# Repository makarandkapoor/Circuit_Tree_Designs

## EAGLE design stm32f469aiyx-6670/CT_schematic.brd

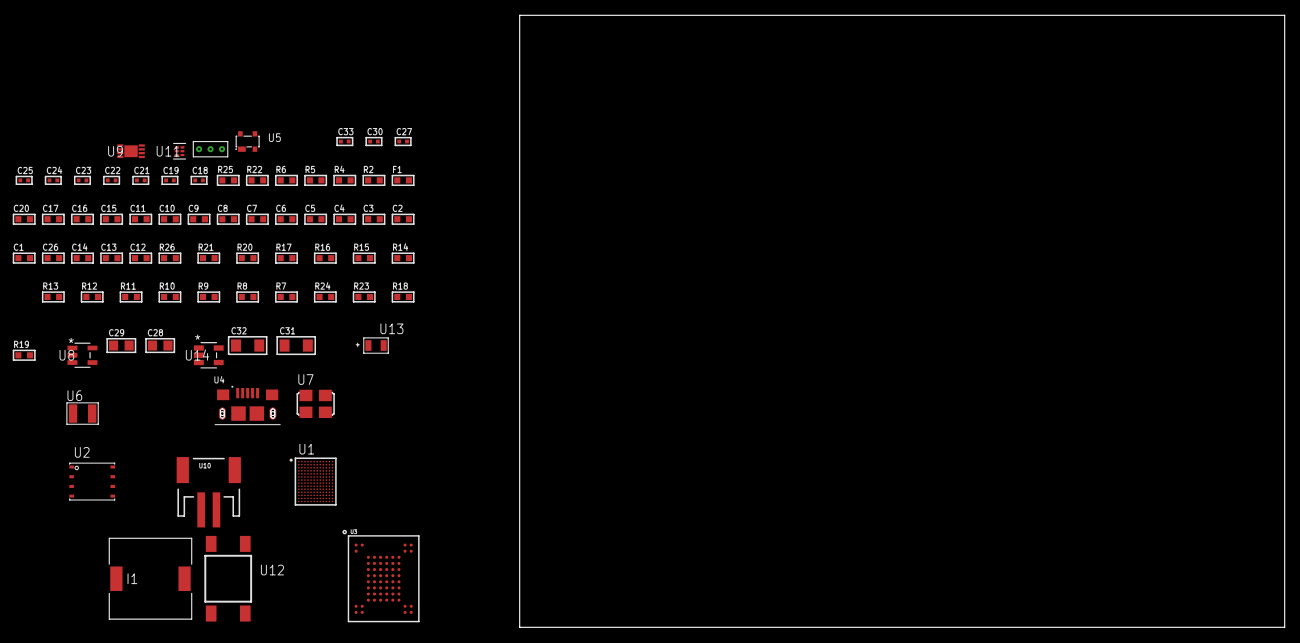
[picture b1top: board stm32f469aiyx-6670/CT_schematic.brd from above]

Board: 2 copper layers, 74 parts (0 on the bottom side), 48 nets, no tracks yet.

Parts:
C1, C16, C20: 1e-06; C0603
C2, C3, C4, C5, C6, C7, C8, C9, C10, C11, C17: 1e-07; C0603
C12: 4.7e-06; C0603
C13, C14, C26: 2.2e-06; C0603
C15: 1e-08; C0603
C18, C19: 1e-11; C0402
C21, C27, C33: 1e-08; C0402
C22, C23, C24, C25, C30: 1e-07; C0402
C28, C29: 1e-05; C0805
C31, C32: 1e-05; C1206
F1: 240.0; L0603
I1: 2.5e-06; DR1040
R2: 1000.0; R0603
R4: 4700.0; R0603
R5, R6: 2200.0; R0603
R7, R8, R9, R10, R11, R12, R13, R14, R15, R16, R17, R20, R21, R26: 10000.0; R0603
R18: 220000.0; R0603
R19: 1000000.0; R0603
R22: 9100.0; R0603
R23: 680000.0; R0603
R24: 120000.0; R0603
R25: 2000.0; R0603
U1: STM32F469AIY6TR; WLCSP168
U2: 24AA512-I/MF; DFN8-S
U3: mt29f4g08abadah4; VFBGA-63
U4: 10118193-0001LF; FCI_10118193-0001LF
U5: prtr5v0u2ax; SOT143B
U6: ABS07-32.768KHZ-7-T
U7: ASFL1-25MHZ-NCS; ASFL1
U8: ltc3406es5; TSOT-23-5
U9: MCP73831T-2ACI/MC; DFN8_2X3MC
U10: S2B-PH-SM4-TB(LF)(SN); JST-2-SMD
U11: TPS3895ADRYR; SON-6
U12: 4-1437565-2; SW_4-1437565-2
U13: Q65110A2395; LGM67K-G1J2-24-Z
U14: nc7sz125m5x; NC7SZ125M5X
U15: Dummy; DUMMY_PACKAGE_165

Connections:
CLK_CRYSTAL_U1_E11: C18.1, U1.E11, U6.1
CLK_CRYSTAL_U1_E12: C19.1, U1.E12, U6.2
CLK_U1_K11: U1.K11, U7.3
GND: C1.2, C2.2, C3.2, C4.2, C5.2, C6.2, C7.2, C8.2, C9.2, C10.2, C11.2, C12.2, C13.2, C14.2, C15.2, C16.2, C17.2, C18.2, C19.2, C20.2, C21.2, C22.2, C23.2, C24.2, C25.2, C26.2, C27.2, C28.2, C29.1, C29.2, C30.2, C31.2, C32.2, C33.2, R2.2, R9.2, R10.2, R11.2, R18.2, R22.2, R24.2, R25.2, U1.A4, U1.B7, U1.B10, U1.C1, U1.F2, U1.F7, U1.F12, U1.H1, U1.H7, U1.J11, U1.L11, U1.M1, U1.N8, U1.N11, U1.P4, U2.4, U3.C5, U3.F7, U3.K3, U3.K8, U4.5, U4.6, U4.7, U4.8, U4.9, U5.1, U7.2, U8.2, U9.6, U9.9, U10.2, U11.2, U13.C, U14.1, U14.3, U15.1
INPUT_USBPOWER_5V: C20.1, C31.1, R26.2, U1.E2, U4.1, U5.4, U9.1, U9.2
NET_U1_A9: R6.1, U1.A9, U2.5
NET_U1_B9: R5.1, U1.B9, U2.6
NET_U1_D2: C14.1, U1.D2
NET_U1_D9: R7.1, U1.D9
NET_U1_F8: R8.1, U1.F8
NET_U1_H9: R4.1, U1.H9, U14.4
NET_U1_M12: C15.1, C16.1, F1.1, U1.M12
NET_U1_N4: C13.1, U1.N4
NET_U1_P9: R9.1, U1.P9
NET_U1_P11: U12.3, U12.4
NET_U2_1: R10.1, U2.1
NET_U2_2: R11.1, U2.2
NET_U2_3: R12.1, U2.3
NET_U3_C3: R17.1, U3.C3
NET_U8_3: I1.1, U8.3
NET_U8_5: R18.1, R19.1, U8.5
NET_U8_ATNET_3: I1.2, R19.2
NET_U9_5: R26.1, U9.5
NET_U9_8: R25.1, U9.8
NET_U11_1: R21.1, R22.1, U11.1
NET_U11_3: R23.2, R24.1, U11.3
NET_U11_4: R20.1, U11.4, U14.2
NET_U12_1: R2.1, U12.1, U12.2
PROC_ADC1_IN3: U1.N10, U15.2
PROC_ADC1_IN4: U1.M9, U15.3
PROC_FMC_A16: U1.J4, U3.D5
PROC_FMC_A17: U1.M2, U3.C4
PROC_FMC_D0: U1.L3, U3.H4
PROC_FMC_D1: U1.L2, U3.J4
PROC_FMC_D2: U1.E6, U3.K4
PROC_FMC_D3: U1.A3, U3.K5
PROC_FMC_D4: U1.N7, U3.K6
PROC_FMC_D5: U1.M7, U3.J7
PROC_FMC_D6: U1.K6, U3.K7
PROC_FMC_D7: U1.P6, U3.J8
PROC_FMC_INT: R13.1, U1.H6, U3.C8
PROC_FMC_NCE: R14.1, U1.D7, U3.C6
PROC_FMC_NOE: R16.1, U1.B4, U3.D4
PROC_FMC_NWE: R15.1, U1.C6, U3.C7
PROC_USB_OTG_FS_DM: U1.F7, U4.2, U5.3
PROC_USB_OTG_FS_DP: U1.F6, U4.3, U5.2
VCC_S1_3V7: C28.1, C32.1, U8.4, U9.3, U9.4, U10.1
VCC_TIER1_3V3: C1.1, C2.1, C3.1, C4.1, C5.1, C6.1, C7.1, C8.1, C9.1, C10.1, C11.1, C12.1, C17.1, C21.1, C22.1, C23.1, C24.1, C25.1, C26.1, C27.1, C29.2, C30.1, C33.1, F1.2, I1.2, R4.2, R5.2, R6.2, R7.2, R8.2, R12.2, R13.2, R14.2, R15.2, R16.2, R17.2, R19.2, R20.2, R21.2, R23.1, U1.A7, U1.A11, U1.B5, U1.C2, U1.C12, U1.F1, U1.G11, U1.J12, U1.L1, U1.P3, U1.P8, U1.P12, U2.7, U2.8, U3.D3, U3.G4, U3.H8, U3.J6, U7.4, U11.6, U14.5

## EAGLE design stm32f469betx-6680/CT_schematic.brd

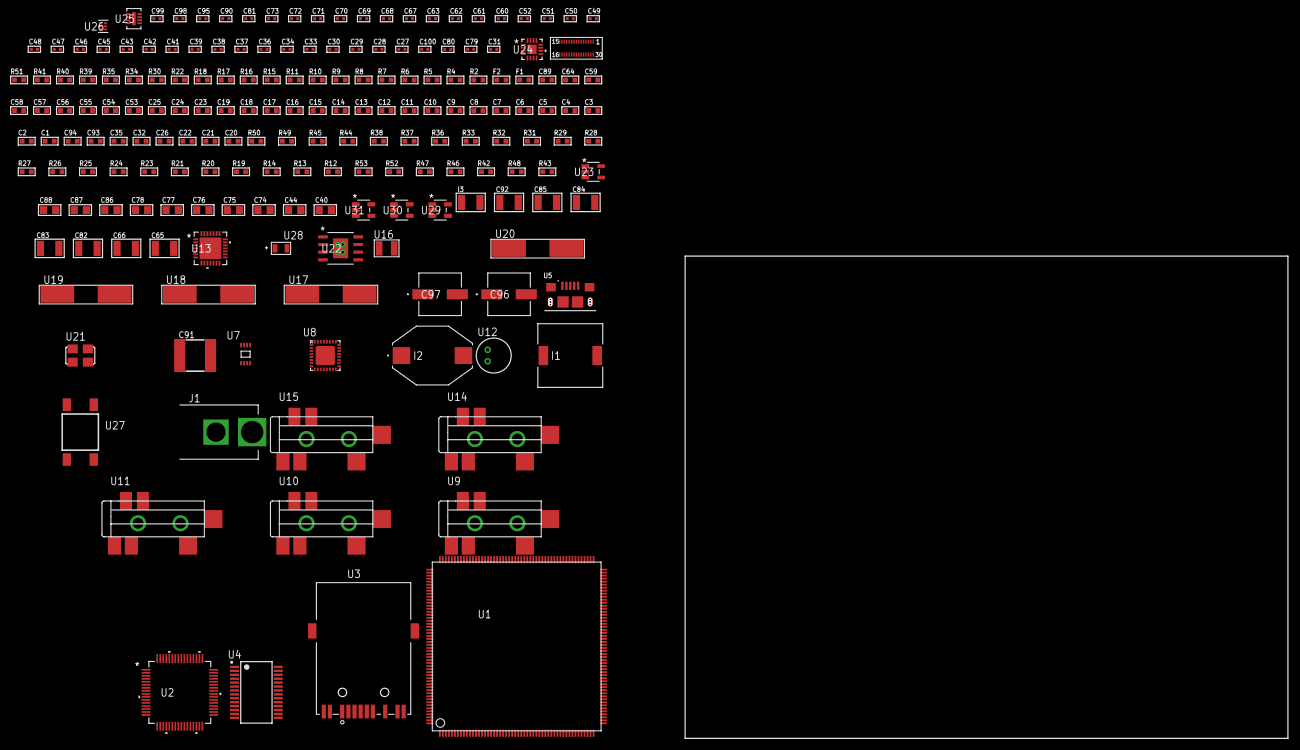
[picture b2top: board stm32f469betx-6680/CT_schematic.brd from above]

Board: 2 copper layers, 122.6 x 80.0 mm, 188 parts (0 on the bottom side), 129 nets, no tracks yet.

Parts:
C1, C24, C53, C54, C55, C56, C57, C58, C59, C64, C89: 1e-06; C0603
C2, C3, C4, C5, C6, C7, C8, C9, C10, C11, C12, C13, C14, C15, C16, C17, C18, C19, C25: 1e-07; C0603
C20: 4.7e-06; C0603
C21, C22, C26, C32, C35, C93: 2.2e-06; C0603
C23: 1e-08; C0603
C27, C28, C29, C30: 1e-11; C0402
C31: 1.8e-08; C0402
C33, C36, C38, C39, C41, C42, C43, C45, C46, C47, C48, C49, C50, C51, C60, C61, C62, C63, C69, C70, C71, C72, C73, C90, C95: 1e-07; C0402
C34, C37, C52, C81, C98, C99, C100: 1e-08; C0402
C40, C74, C75, C76, C77, C78, C86, C87, C88: 1e-05; C0805
C44: 4.7e-06; C0805
C65, C66: 2.2e-05; C1210
C67, C68: 1e-09; C0402
C79, C80: 2.2e-11; C0402
C82, C83, C84, C85, C92: 1e-05; C1210
C91: 6.8e-05; 2220
C94: 2.2e-07; C0603
C96, C97: 0.0001; EXV-9H
F1: 240.0; L0603
F2: 510.0; L0603
I1: 7e-06; DR1040
I2: 1.5e-06; IND_PM3316
I3: 1e-05; L1210
J1: PJ-037B; PJ-037B_PACKAGE
R2: 1000.0; R0603
R4, R5, R6, R30: 4700.0; R0603
R7, R8, R9, R10, R11, R41: 2200.0; R0603
R12, R13, R14, R19, R20, R21, R23, R24, R25, R26, R27, R28, R29, R31, R32, R33, R49, R50: 10000.0; R0603
R15, R16: 0.1; R0603
R17, R18: 200.0; R0603
R22, R34, R35: 1270.0; R0603
R36, R37, R38: 47000.0; R0603
R39: 680.0; R0603
R40: 910.0; R0603
R42: 270000.0; R0603
R43: 1000000.0; R0603
R44: 20000.0; R0603
R45: 91000.0; R0603
R46: 300000.0; R0603
R47: 100000.0; R0603
R48: 1600000.0; R0603
R51: 9100.0; R0603
R52: 680000.0; R0603
R53: 120000.0; R0603
U1: STM32F469BET6; LQFP208
U2: BCM5221KPT; TQFP64_10X10MC
U3: 7498011122R
U4: FT232RL-REEL; SSOP-28
U5: 10118193-0001LF; FCI_10118193-0001LF
U6: LH430WV2-SD01
U7: 24AA04-I/MC; TDFN-8/6MM
U8: SGTL5000XNAA3; QFN-32
U9, U10, U11, U14, U15: SJ-43515TS-SMT-TR
U12: WM-64PCT; WM-64PC
U13: WM8731CLSEFL; QFN-28
U16: ABS07-32.768KHZ-7-T
U17, U18: ABLS-25.000MHZ-B2F-T
U19: ABLS-12.000MHZ-B4-T
U20: ABLS-12.288MHZ-B4-T
U21: ASFL-24.57MHZ-NCS; ASFL1
U22: MIC5234YME; SOIC-8_EP
U23: ltc3406es5; TSOT-23-5
U24: LTC3601EUD#PBF; QFN-16_EP
U25: LT3494AEDDB#TRMPBF; DFN-8_DDB
U26: TPS3895ADRYR; SON-6
U27: 4-1437565-2; SW_4-1437565-2
U28: Q65110A2395; LGM67K-G1J2-24-Z
U29, U30, U31: nc7sz125m5x; NC7SZ125M5X

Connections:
CLK_CRYSTAL_U1_9: C27.1, U1.9, U16.1
CLK_CRYSTAL_U1_10: C28.1, U1.10, U16.2
CLK_CRYSTAL_U1_32: C29.1, U1.32, U17.1
CLK_CRYSTAL_U1_33: C30.1, U1.33, U17.2
CLK_CRYSTAL_U2_5: U2.5, U18.2
CLK_CRYSTAL_U2_6: U2.6, U18.1
CLK_CRYSTAL_U4_27: U4.27, U19.1
CLK_CRYSTAL_U4_28: U4.28, U19.2
CLK_CRYSTAL_U13_1: C79.1, U13.1, U20.1
CLK_CRYSTAL_U13_2: C80.1, U13.2, U20.2
CLK_U8_21: U8.21, U21.3
GND: C1.2, C2.2, C3.2, C4.2, C5.2, C6.2, C7.2, C8.2, C9.2, C10.2, C11.2, C12.2, C13.2, C14.2, C15.2, C16.2, C17.2, C18.2, C19.2, C20.2, C21.2, C22.2, C23.2, C24.2, C25.2, C26.2, C27.2, C28.2, C29.2, C30.2, C31.2, C32.2, C33.2, C34.2, C35.2, C36.2, C37.2, C38.2, C39.2, C40.2, C41.2, C42.2, C43.2, C44.2, C45.2, C46.2, C47.2, C48.2, C49.2, C50.2, C51.2, C52.2, C60.2, C61.2, C62.2, C63.2, C64.2, C68.2, C69.2, C70.2, C71.2, C72.2, C73.2, C74.2, C75.2, C76.2, C77.2, C78.2, C79.2, C80.2, C81.2, C82.2, C83.2, C84.2, C85.2, C86.2, C87.1, C87.2, C88.2, C89.2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
NET_U1_34: R6.1, U1.34, U31.4
NET_U1_36: R9.1, U1.36, U2.42
NET_U1_42: C23.1, C24.1, F1.1, U1.41, U1.42
NET_U1_45: R10.1, U1.45, U2.41
NET_U1_63: R14.1, U1.63
NET_U1_92: C21.1, U1.92
NET_U1_125: C26.1, U1.119, U1.125
NET_U1_148: C22.1, U1.148
NET_U1_195: R7.1, U1.195, U7.6
NET_U1_196: R8.1, U1.196, U7.5
NET_U1_197: R13.1, U1.197
NET_U1_203: R12.1, U1.203
NET_U1_208: U27.3, U27.4
NET_U2_2: C35.1, C36.1, C37.1, U2.2, U2.55
NET_U2_9: R5.1, U2.9, U30.4
NET_U2_10: R23.1, U2.10
NET_U2_11: R24.1, U2.11
NET_U2_12: R25.1, U2.12
NET_U2_13: R26.1, U2.13
NET_U2_14: R27.1, U2.14
NET_U2_16: R21.1, U2.16
NET_U2_18: R29.1, U2.18
NET_U2_23: R22.1, U2.23
NET_U2_27: C32.1, C33.1, C34.1, U2.22, U2.27, U2.28
NET_U2_37: R28.1, U2.37
NET_U2_38: R19.1, U2.38
NET_U2_39: R20.1, U2.39
NET_U3_1: U2.31, U3.1
NET_U3_2: F2.2, U3.2
NET_U3_3: U2.30, U3.3
NET_U3_4: U2.26, U3.4
NET_U3_5: C31.1, F2.1, U3.2, U3.5
NET_U3_6: U2.25, U3.6
NET_U3_8: R16.1, U3.8
NET_U3_9: R17.1, U3.9
NET_U3_11: R18.1, U3.11
NET_U3_12: R17.2, U3.12
NET_U3_13: R15.1, U3.13, U3.14
NET_U4_14: R31.1, U4.14
NET_U4_17: C45.1, U4.17
NET_U4_19: R32.1, U4.19
NET_U5_1: R30.1, U5.1
NET_U5_2: U4.16, U5.2
NET_U5_3: U4.15, U5.3
NET_U6_4: R4.1, U6.4, U29.4
NET_U6_20: R33.1, U6.20
NET_U8_10: C63.1, U8.10
NET_U8_29: R34.1, U8.29
NET_U8_31: R35.1, U8.31
NET_U9_1: U8.4, U9.1
NET_U9_2: U8.2, U9.2
NET_U9_5: U8.6, U9.5
NET_U10_2: C54.1, U10.2
NET_U10_5: C53.1, U10.5
NET_U11_2: C56.1, C57.1, U11.2
NET_U11_5: C55.1, U11.5
NET_U11_13: C56.2, C57.2
NET_U12_1: C58.1, C59.1, C64.1, U8.16, U12.1
NET_U12_15: C58.2, C59.2
NET_U13_20: C73.1, C78.1, U13.20
NET_U14_2: C66.1, R37.1, U14.2
NET_U14_5: C65.1, R36.1, U14.5
NET_U15_5: C67.1, C68.1, R38.1, R39.1, U15.5
NET_U22_4: R40.2, R41.1, U22.4
NET_U23_3: I1.1, U23.3
NET_U23_5: R42.1, R43.1, U23.5
NET_U23_ATNET_3: I1.2, R43.2
NET_U24_3: C90.2, I2.1, U24.3, U24.4
NET_U24_6: C90.1, U24.6
NET_U24_7: C89.1, U24.7, U24.12
NET_U24_10: R46.1, U24.10
NET_U24_11: R44.1, R45.1, U24.11
NET_U24_ATNET_3: I2.2, R45.2
NET_U25_1: I3.1, U25.1
NET_U25_5: R47.1, U25.5
NET_U25_6: R48.1, U25.6
NET_U25_8: C94.1, U25.8
NET_U26_1: R50.1, R51.1, U26.1
NET_U26_3: R52.2, R53.1, U26.3
NET_U26_4: R49.1, U26.4, U29.2, U30.2, U31.2
NET_U27_1: R2.1, U27.1, U27.2
PROC_DSIHOST_CKN: U1.124, U6.13
PROC_DSIHOST_CKP: U1.123, U6.14
PROC_DSIHOST_D0N: U1.121, U6.7
PROC_DSIHOST_D0P: U1.120, U6.8
PROC_DSIHOST_D1N: U1.127, U6.10
PROC_DSIHOST_D1P: U1.126, U6.11
PROC_ETH_COL: U1.47, U2.61
PROC_ETH_CRS: U1.43, U2.62
PROC_ETH_RXD0: U1.57, U2.48
PROC_ETH_RXD1: U1.58, U2.47
PROC_ETH_RXD2: U1.61, U2.44
PROC_ETH_RXD3: U1.62, U2.43
PROC_ETH_RX_CLK: U1.44, U2.50
PROC_ETH_RX_DV: U1.56, U2.49
PROC_ETH_RX_ER: U1.12, U2.51
PROC_ETH_TXD0: U1.104, U2.57
PROC_ETH_TXD1: U1.105, U2.58
PROC_ETH_TXD2: U1.37, U2.59
PROC_ETH_TXD3: U1.1, U2.60
PROC_ETH_TX_CLK: U1.38, U2.53
PROC_ETH_TX_EN: U1.91, U2.56
PROC_I2S2_CK: U1.90, U8.24
PROC_I2S2_EXT_SD: U1.106, U8.25
PROC_I2S2_SD: U1.107, U8.26
PROC_I2S2_WS: U1.154, U8.23
PROC_I2S3_CK: U1.192, U13.7
PROC_I2S3_EXT_SD: U1.193, U13.10
PROC_I2S3_SD: U1.163, U13.8
PROC_I2S3_WS: U1.53, U13.9, U13.11
PROC_UART4_RX: U1.162, U4.1
PROC_UART4_TX: U1.161, U4.5
VCC_S1_4V6: C82.1, C83.1, C86.1, C88.1, C92.1, C96.1, C97.1, I3.2, J1.1, R47.2, U22.5, U22.8, U23.4, U24.15, U24.16, U25.3, U25.4
VCC_TIER1_1V5: C60.1, C84.1, C85.1, R40.1, U6.29, U8.30, U22.1
VCC_TIER1_2V8: C49.1, C50.1, C51.1, C87.2, I1.2, R43.2, U6.16, U6.21, U6.22, U6.23
VCC_TIER1_3V3: C1.1, C2.1, C3.1, C4.1, C5.1, C6.1, C7.1, C8.1, C9.1, C10.1, C11.1, C12.1, C13.1, C14.1, C15.1, C16.1, C17.1, C18.1, C19.1, C20.1, C25.1, C38.1, C39.1, C40.1, C41.1, C42.1, C43.1, C44.1, C46.1, C47.1, C52.1, C61.1, C62.1, C69.1, C70.1, C71.1, C72.1, C74.1, C75.1, C76.1, C77.1, C81.1, C91.2, C95.1, C98.1, C99.1, C100.1, F1.2, I2.2, R4.2, R5.2, R6.2, R7.2, R8.2, R9.2, R10.2, R11.2, R12.2, R13.2, R20.2, R24.2, R29.2, R31.2, R34.2, R45.2, R49.2, R50.2, R52.1, U1.6, U1.15, U1.26, U1.39, U1.52, U1.59, U1.73, U1.83, U1.94, U1.103, U1.115, U1.118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
VCC_TIER1_12V0: C48.1, C93.1, R48.2, U6.30, U25.7

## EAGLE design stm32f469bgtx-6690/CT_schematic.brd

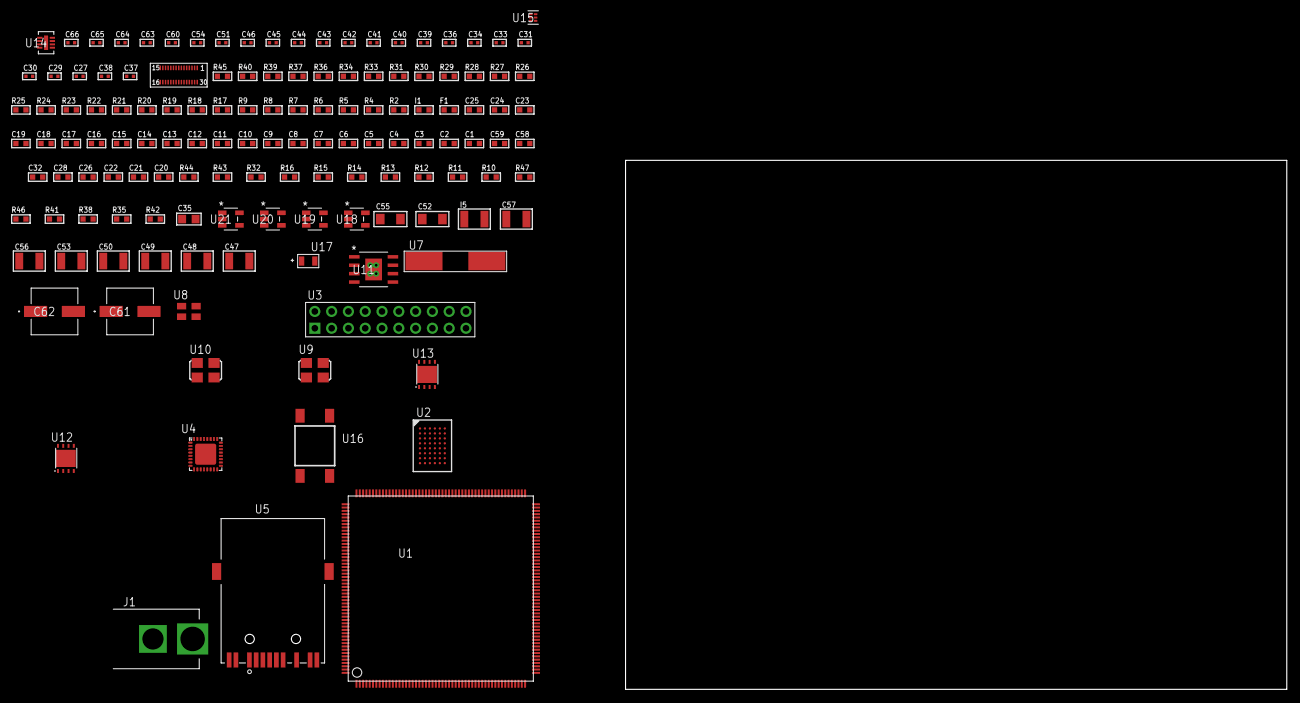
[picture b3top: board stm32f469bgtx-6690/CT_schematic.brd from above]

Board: 2 copper layers, 100.0 x 80.0 mm, 136 parts (0 on the bottom side), 115 nets, no tracks yet.

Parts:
C1, C24: 1e-06; C0603
C2, C3, C4, C5, C6, C7, C8, C9, C10, C11, C12, C13, C14, C15, C16, C17, C18, C19, C25: 1e-07; C0603
C20: 4.7e-06; C0603
C21, C22, C26, C28, C32, C58: 2.2e-06; C0603
C23: 1e-08; C0603
C27, C29, C30, C31, C33, C34, C36, C39, C40, C41, C42, C43, C60: 1e-07; C0402
C35: 1e-05; C0805
C37, C38: 2.2e-11; C0402
C44, C45, C46, C51, C54, C63, C64, C65, C66: 1e-08; C0402
C47, C48, C49, C50, C53, C56, C57: 1e-05; C1210
C52, C55: 1e-05; C1206
C59: 2.2e-07; C0603
C61, C62: 0.0001; EXV-9H
F1: 240.0; L0603
I1: 97.0; R0603
I5: 1e-05; L1210
J1: PJ-037B; PJ-037B_PACKAGE
R2, R24, R25, R26, R28, R30, R37, R40: 1000.0; R0603
R4, R5, R6, R22, R23, R27, R29, R31: 4700.0; R0603
R7, R8, R9, R34: 2200.0; R0603
R10, R11, R12, R13, R14, R15, R16, R32, R43, R44: 10000.0; R0603
R17, R18: 0.1; R0603
R19: 200.0; R0603
R20: 220.0; R0603
R21: 6490.0; R0603
R33: 910.0; R0603
R35, R38, R41: 100000.0; R0603
R36: 1800.0; R0603
R39: 2231.0; R0603
R42: 1600000.0; R0603
R45: 9100.0; R0603
R46: 680000.0; R0603
R47: 120000.0; R0603
U1: STM32F469BGT6; LQFP208
U2: CY62147GE30-45BVXI; VFBGA48
U3: TST-110-05-T-D-RA
U4: KSZ8081RNBIA-TR; QFN-32
U5: 7498011122R
U6: LH430WV2-SD01
U7: ABLS-25.000MHZ-B2F-T
U8: ASEK-32.768KHz-ECST; ASEK
U9: ASFL1-25MHZ-NCS; ASFL1
U10: ASFL1-50MHZ-NCS; ASFL1
U11: MIC5234YME; SOIC-8_EP
U12, U13: LP3878SDX-ADJ/NOPB; WSON-8
U14: LT3494AEDDB#TRMPBF; DFN-8_DDB
U15: TPS3895ADRYR; SON-6
U16: 4-1437565-2; SW_4-1437565-2
U17: Q65110A2395; LGM67K-G1J2-24-Z
U18, U19, U20, U21: nc7sz125m5x; NC7SZ125M5X

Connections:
CLK_CRYSTAL_U4_8: C37.1, U4.8, U7.2
CLK_CRYSTAL_U4_9: C38.1, U4.9, U7.1
CLK_U1_9: U1.9, U8.3
CLK_U1_32: U1.32, U9.3
CLK_U1_44: U1.44, U10.3
GND: C1.2, C2.2, C3.2, C4.2, C5.2, C6.2, C7.2, C8.2, C9.2, C10.2, C11.2, C12.2, C13.2, C14.2, C15.2, C16.2, C17.2, C18.2, C19.2, C20.2, C21.2, C22.2, C23.2, C24.2, C25.2, C26.2, C27.2, C28.2, C29.2, C30.2, C31.2, C32.2, C33.2, C34.2, C35.2, C36.2, C37.2, C38.2, C39.2, C40.2, C41.2, C42.2, C43.2, C44.2, C45.2, C46.2, C47.2, C48.2, C49.2, C50.2, C51.2, C52.2, C53.2, C54.2, C55.2, C56.2, C57.2, C58.2, C59.2, C60.2, C61.2, C62.2, C63.2, C64.2, C65.2, C66.2, J1.2, R2.2, R12.2, R17.2, R18.2, R21.2, R23.2, R24.2, R25.2, R26.2, R28.2, R30.2, R32.2, R34.2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
NET_U1_34: R6.1, U1.34, U21.4
NET_U1_36: R7.1, U1.36, U4.12
NET_U1_42: C23.1, C24.1, F1.1, U1.41, U1.42
NET_U1_45: R8.1, U1.45, U4.11
NET_U1_63: R12.1, U1.63
NET_U1_92: C21.1, U1.92
NET_U1_125: C26.1, U1.119, U1.125
NET_U1_148: C22.1, U1.148
NET_U1_197: R11.1, U1.197
NET_U1_203: R10.1, U1.203
NET_U1_208: U16.3, U16.4
NET_U4_2: C32.1, C33.1, U4.2
NET_U4_3: C34.1, I1.1, U4.3
NET_U4_10: R21.1, U4.10
NET_U4_13: R24.1, U4.13
NET_U4_14: R25.1, U4.14
NET_U4_19: R23.1, U4.19
NET_U4_20: R29.1, U4.20
NET_U4_21: R22.1, U4.21
NET_U4_28: R27.1, U4.28
NET_U4_29: R28.1, U4.29
NET_U4_31: R30.1, U4.31
NET_U4_32: R5.1, U4.32, U20.4
NET_U5_1: U4.7, U5.1
NET_U5_2: C30.1, U5.2
NET_U5_3: U4.6, U5.3
NET_U5_4: U4.5, U5.4
NET_U5_5: C31.1, U5.5
NET_U5_6: U4.4, U5.6
NET_U5_8: R18.1, U5.8
NET_U5_9: R19.1, U5.9
NET_U5_12: R20.1, U5.12
NET_U5_13: R17.1, U5.13, U5.14
NET_U6_4: R4.1, U6.4, U19.4
NET_U6_20: R32.1, U6.20
NET_U11_4: R33.2, R34.1, U11.4
NET_U12_1: C51.1, U12.1
NET_U12_6: R36.2, R37.1, U12.6
NET_U12_8: R35.1, U12.8
NET_U13_1: C54.1, U13.1
NET_U13_6: R39.2, R40.1, U13.6
NET_U13_8: R38.1, U13.8
NET_U14_1: I5.1, U14.1
NET_U14_5: R41.1, U14.5
NET_U14_6: R42.1, U14.6
NET_U14_8: C59.1, U14.8
NET_U15_1: R44.1, R45.1, U15.1
NET_U15_3: R46.2, R47.1, U15.3
NET_U15_4: R43.1, U15.4, U18.4, U19.2, U20.2, U21.2
NET_U16_1: R2.1, U16.1, U16.2
PROC_DSIHOST_CKN: U1.124, U6.13
PROC_DSIHOST_CKP: U1.123, U6.14
PROC_DSIHOST_D0N: U1.121, U6.7
PROC_DSIHOST_D0P: U1.120, U6.8
PROC_DSIHOST_D1N: U1.127, U6.10
PROC_DSIHOST_D1P: U1.126, U6.11
PROC_ETH_CRS_DV: U1.56, U4.18
PROC_ETH_RXD0: R31.1, U1.57, U4.16
PROC_ETH_RXD1: R26.1, U1.58, U4.15
PROC_ETH_TXD0: U1.104, U4.24
PROC_ETH_TXD1: U1.105, U4.25
PROC_ETH_TX_EN: U1.91, U4.23
PROC_FMC_A0: U1.16, U2.A3
PROC_FMC_A1: U1.17, U2.A4
PROC_FMC_A2: U1.18, U2.A5
PROC_FMC_A3: U1.22, U2.B3
PROC_FMC_A4: U1.23, U2.B4
PROC_FMC_A5: U1.24, U2.C3
PROC_FMC_A6: U1.71, U2.C4
PROC_FMC_A7: U1.74, U2.D4
PROC_FMC_A8: U1.75, U2.H2
PROC_FMC_A9: U1.76, U2.H3
PROC_FMC_A10: U1.77, U2.H4
PROC_FMC_A11: U1.78, U2.H5
PROC_FMC_A12: U1.129, U2.G3
PROC_FMC_A13: U1.130, U2.G4
PROC_FMC_A14: U1.131, U2.F3
PROC_FMC_A15: U1.132, U2.F4
PROC_FMC_A16: U1.111, U2.E4
PROC_FMC_A17: U1.112, U2.D3
PROC_FMC_D0: U1.116, U2.B6
PROC_FMC_D1: U1.117, U2.C5
PROC_FMC_D2: U1.164, U2.C6
PROC_FMC_D3: U1.165, U2.D5
PROC_FMC_D4: U1.79, U2.E5
PROC_FMC_D5: U1.80, U2.F5
PROC_FMC_D6: U1.81, U2.F6
PROC_FMC_D7: U1.84, U2.G6
PROC_FMC_D8: U1.85, U2.B1
PROC_FMC_D9: U1.86, U2.C1
PROC_FMC_D10: U1.87, U2.C2
PROC_FMC_D11: U1.88, U2.D2
PROC_FMC_D12: U1.89, U2.E2
PROC_FMC_D13: U1.108, U2.F2
PROC_FMC_D14: U1.109, U2.F1
PROC_FMC_D15: U1.110, U2.G1
PROC_FMC_NBL0: U1.200, U2.A1
PROC_FMC_NE2: R14.1, U1.178, U2.B5
PROC_FMC_NOE: R13.1, U1.168, U2.A2
PROC_FMC_NWE: R15.1, U1.169, U2.G5
PROC_SYS_JTCK_SWCLK: U1.159, U3.9
PROC_SYS_JTDO_SWO: U1.192, U3.13
PROC_SYS_JTMS_SWDIO: U1.147, U3.7
RST_OUT_U3_SRESET_B: R16.1, U3.15, U18.1
VCC_S1_7V5: C47.1, C48.1, C52.1, C55.1, C57.1, C61.1, C62.1, I5.2, J1.1, R35.2, R38.2, R41.2, U11.5, U11.8, U12.4, U13.4, U14.3, U14.4
VCC_TIER1_1V5: C49.1, C50.1, R33.1, U6.29, U11.1
VCC_TIER1_2V8: C41.1, C42.1, C43.1, C53.1, R36.1, U6.16, U6.21, U6.22, U6.23, U12.5
VCC_TIER1_3V3: C1.1, C2.1, C3.1, C4.1, C5.1, C6.1, C7.1, C8.1, C9.1, C10.1, C11.1, C12.1, C13.1, C14.1, C15.1, C16.1, C17.1, C18.1, C19.1, C20.1, C25.1, C27.1, C28.1, C29.1, C35.1, C36.1, C39.1, C44.1, C45.1, C46.1, C56.1, C60.1, C63.1, C64.1, C65.1, C66.1, F1.2, I1.2, R4.2, R5.2, R6.2, R7.2, R8.2, R9.2, R10.2, R11.2, R13.2, R14.2, R15.2, R16.2, R22.2, R27.2, R29.2, R31.2, R39.1, R43.2, R44.2, R46.1, U1.6, U1.15, U1.26, U1.39, U1.52, U1.59, U1.73, U1.83, U1.94, U1.103, U1.115, U1.118, U1.137, U1.150, U1.158, U1.171, U1.185, U1.204, U2.D6, U2.E1, U3.1, U4.17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
VCC_TIER1_12V0: C40.1, C58.1, R42.2, U6.30, U14.7

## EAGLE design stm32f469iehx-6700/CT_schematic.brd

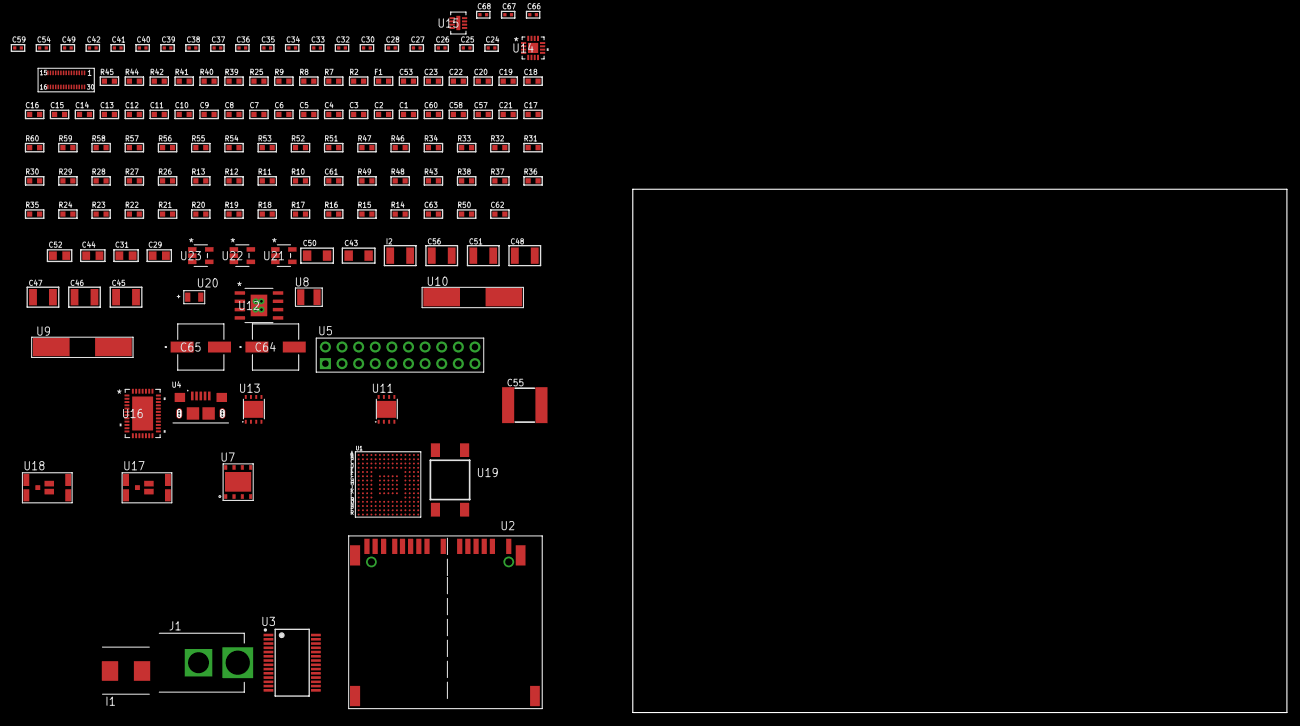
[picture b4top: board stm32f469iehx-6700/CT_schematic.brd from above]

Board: 2 copper layers, 150 parts (0 on the bottom side), 96 nets, no tracks yet.

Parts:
C1, C19, C53: 1e-06; C0603
C2, C3, C4, C5, C6, C7, C8, C9, C10, C11, C12, C13, C14, C15, C16, C20, C22, C23: 1e-07; C0603
C17: 4.7e-06; C0603
C18: 1e-08; C0603
C21, C57, C60: 2.2e-06; C0603
C24, C25, C26, C27: 1e-11; C0402
C28, C30, C32, C33, C34, C35, C36, C37, C38, C39, C40, C41, C54, C59: 1e-07; C0402
C29, C44, C52: 1e-05; C0805
C31: 4.7e-06; C0805
C42, C49, C66, C67, C68: 1e-08; C0402
C43, C50: 1e-05; C1206
C45, C46, C47, C48, C51, C56: 1e-05; C1210
C55: 6.8e-05; 2220
C58: 2.2e-07; C0603
C61: 2.45e-08; R0603
C62: 2.8258362168397e-09; R0603
C63: 7.105e-09; R0603
C64, C65: 0.0001; EXV-9H
F1: 240.0; L0603
I1: 3.3e-06; WE-HCI_7030/7040/7050
I2: 1e-05; L1210
J1: PJ-037B; PJ-037B_PACKAGE
R2, R40, R45: 1000.0; R0603
R7, R8, R25: 4700.0; R0603
R9, R42: 2200.0; R0603
R10, R11, R12, R13, R26, R27, R28, R29, R30, R31, R32, R33, R34, R51, R53, R54, R57, R58, R59: 10000.0; R0603
R14, R15, R16, R17, R18, R19, R20, R21, R22, R23, R24, R35, R36, R37, R38, R43, R49: 100000.0; R0603
R39: 200.0; R0603
R41: 910.0; R0603
R44: 1800.0; R0603
R46: 20000.0; R0603
R47: 91000.0; R0603
R48: 300000.0; R0603
R50: 1600000.0; R0603
R52: 75000.0; R0603
R55, R56: 95300.0; R0603
R60: 47000.0; R0603
U1: STM32F469IEH6; UFBGA176
U2: 10100565
U3: FT232RL-REEL; SSOP-28
U4: 10118193-0001LF; FCI_10118193-0001LF
U5: TST-110-05-T-D-RA
U6: LH430WV2-SD01
U7: SST26VF016B-104I/MF; WFDN-8
U8: ABS07-32.768KHZ-7-T
U9: ABLS-25.000MHZ-B2F-T
U10: ABLS-12.000MHZ-B4-T
U11, U13: LP3878SDX-ADJ/NOPB; WSON-8
U12: MIC5234YME; SOIC-8_EP
U14: LTC3601EUD#PBF; QFN-16_EP
U15: LT3494AEDDB#TRMPBF; DFN-8_DDB
U16: LTC2928CUHF#PBF; QFN-38_UHF
U17, U18: IRF8306MTRPbF; IRF8306MTRPBF
U19: 4-1437565-2; SW_4-1437565-2
U20: Q65110A2395; LGM67K-G1J2-24-Z
U21, U22, U23: nc7sz125m5x; NC7SZ125M5X

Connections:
CLK_CRYSTAL_U1_E1: C24.1, U1.E1, U8.1
CLK_CRYSTAL_U1_F1: C25.1, U1.F1, U8.2
CLK_CRYSTAL_U1_G1: C26.1, U1.G1, U9.1
CLK_CRYSTAL_U1_H1: C27.1, U1.H1, U9.2
CLK_CRYSTAL_U3_27: U3.27, U10.1
CLK_CRYSTAL_U3_28: U3.28, U10.2
GND: C1.2, C2.2, C3.2, C4.2, C5.2, C6.2, C7.2, C8.2, C9.2, C10.2, C11.2, C12.2, C13.2, C14.2, C15.2, C16.2, C17.2, C18.2, C19.2, C20.2, C21.2, C22.2, C23.2, C24.2, C25.2, C26.2, C27.2, C28.2, C29.2, C30.2, C31.2, C32.2, C33.2, C34.2, C35.2, C36.2, C37.2, C38.2, C39.2, C40.2, C41.2, C42.2, C43.2, C44.2, C45.2, C46.2, C47.2, C48.2, C49.2, C50.2, C51.2, C52.2, C53.2, C55.1, C55.2, C56.2, C57.2, C58.2, C59.2, C60.2, C61.2, C62.2, C63.2, C64.2, C65.2, C66.2, C67.2, C68.2, J1.2, R2.2, R27.2, R33.2, R34.2, R40.2, R42.2, R45.2, R46.2, R48.2, R52.2, R55.2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
NET_U1_C6: R10.1, U1.C6
NET_U1_D6: R11.1, U1.D6
NET_U1_D13: C21.1, U1.D13, U1.K12
NET_U1_F13: C23.1, U1.F13
NET_U1_J1: R8.1, U1.J1, U23.4
NET_U1_L4: R13.1, U1.L4
NET_U1_M6: R12.1, U1.M6
NET_U1_R1: C18.1, C19.1, F1.1, U1.P1, U1.R1
NET_U1_R15: U19.3, U19.4
NET_U2_1: R16.1, U2.1
NET_U2_2: R15.1, U2.2
NET_U2_18: U2.18, U2.19
NET_U3_14: R26.1, U3.14
NET_U3_17: C32.1, U3.17
NET_U3_19: R27.1, U3.19
NET_U4_1: R25.1, U4.1
NET_U4_2: U3.16, U4.2
NET_U4_3: U3.15, U4.3
NET_U5_19: R33.1, U5.19
NET_U6_4: R7.1, U6.4, U22.4
NET_U6_20: R34.1, U6.20
NET_U11_1: C42.1, U11.1
NET_U11_6: R39.2, R40.1, U11.6
NET_U11_8: R38.1, U11.8
NET_U12_4: R41.2, R42.1, U12.4
NET_U13_1: C49.1, U13.1
NET_U13_6: R44.2, R45.1, U13.6
NET_U13_8: R43.1, U13.8
NET_U14_3: C54.2, I1.1, U14.3, U14.4
NET_U14_6: C54.1, U14.6
NET_U14_7: C53.1, U14.7, U14.12
NET_U14_10: R48.1, U14.10
NET_U14_11: R46.1, R47.1, U14.11
NET_U14_ATNET_3: I1.2, R47.2
NET_U15_1: I2.1, U15.1
NET_U15_5: R49.1, U15.5
NET_U15_6: R50.1, U15.6
NET_U15_8: C58.1, U15.8
NET_U16_3: R58.1, U16.3
NET_U16_6: R55.1, U16.6
NET_U16_7: R56.1, U16.7
NET_U16_16: R57.1, R60.1, U16.16
NET_U16_18: R54.1, U16.18
NET_U16_19: R53.1, U16.19, U16.20
NET_U16_21: R51.1, R52.1, U16.21, U21.4, U22.2, U23.2
NET_U16_26: C62.1, U16.26
NET_U16_27: C61.1, U16.27
NET_U16_28: C63.1, U16.28
NET_U16_38: R59.1, U16.38
NET_U17_3: U16.2, U17.3
NET_U18_3: U16.37, U18.3
NET_U19_1: R2.1, U19.1, U19.2
PROC_DSIHOST_CKN: U1.L13, U6.13
PROC_DSIHOST_CKP: U1.L12, U6.14
PROC_DSIHOST_D0N: U1.M13, U6.7
PROC_DSIHOST_D0P: U1.M12, U6.8
PROC_DSIHOST_D1N: U1.E13, U6.10
PROC_DSIHOST_D1P: U1.E12, U6.11
PROC_QUADSPI_BK1_IO0: U1.L3, U7.5
PROC_QUADSPI_BK1_IO1: U1.L2, U7.2
PROC_QUADSPI_BK1_IO2: R36.1, U1.A2, U7.3
PROC_QUADSPI_BK1_IO3: R37.1, U1.M15, U7.7
PROC_QUADSPI_BK1_NCS: R35.1, U1.B6, U7.1
PROC_QUADSPI_CLK: U1.L1, U7.6
PROC_SDIO_CK: R14.1, U1.A12, U2.8
PROC_SDIO_D0: R17.1, U1.G14, U2.4
PROC_SDIO_D1: R18.1, U1.F14, U2.3
PROC_SDIO_D2: R19.1, U1.B14, U2.15
PROC_SDIO_D3: R20.1, U1.B13, U2.14
PROC_SDIO_D4: R21.1, U1.A5, U2.13
PROC_SDIO_D5: R22.1, U1.B4, U2.11
PROC_SDIO_D6: R23.1, U1.H15, U2.7
PROC_SDIO_D7: R24.1, U1.G15, U2.5
PROC_SYS_JTCK_SWCLK: R31.1, U1.A14, U5.9
PROC_SYS_JTDI: R29.1, U1.A13, U5.5
PROC_SYS_JTDO_SWO: U1.A10, U5.13
PROC_SYS_JTMS_SWDIO: R30.1, U1.A15, U5.7
PROC_SYS_JTRST: R28.1, U1.A9, U5.3
PROC_UART7_RX: U1.K2, U3.1
PROC_UART7_TX: U1.K1, U3.5
RST_OUT_U5_SRESET_B: R32.1, U5.15, U21.1
VCC_6V2: C59.1, C60.1, C64.1, C65.1, J1.1, R51.2, R53.2, R54.2, R60.2, U16.11, U16.22, U17.1, U17.2, U17.6, U17.7, U18.1, U18.2, U18.6, U18.7
VCC_S1_6V2: C43.1, C45.1, C46.1, C50.1, C52.1, C56.1, I2.2, R38.2, R43.2, R49.2, U11.4, U12.5, U12.8, U13.4, U14.15, U14.16, U15.3, U15.4, U17.4, U17.5
VCC_S2_6V2: U18.4, U18.5
VCC_TIER1_1V2: C22.1, C44.1, R39.1, U1.M10, U11.5
VCC_TIER1_1V5: C47.1, C48.1, R41.1, U6.29, U12.1
VCC_TIER1_2V8: C38.1, C39.1, C40.1, C51.1, R44.1, U6.16, U6.21, U6.22, U6.23, U13.5
VCC_TIER1_3V3: C1.1, C2.1, C3.1, C4.1, C5.1, C6.1, C7.1, C8.1, C9.1, C10.1, C11.1, C12.1, C13.1, C14.1, C15.1, C16.1, C17.1, C20.1, C28.1, C29.1, C30.1, C31.1, C33.1, C34.1, C35.1, C36.1, C41.1, C55.2, C66.1, C67.1, C68.1, F1.2, I1.2, R7.2, R8.2, R9.2, R10.2, R11.2, R12.2, R13.2, R14.2, R15.2, R16.2, R17.2, R18.2, R19.2, R20.2, R21.2, R22.2, R23.2, R24.2, R26.2, R28.2, R29.2, R30.2, R31.2, R32.2, R35.2, R36.2, R37.2, R47.2, U1.C1, U1.C5, U1.C7, U1.C8, U1.C9, U1.F3, U1.G3, U1.G13, U1.H13, U1.J12, U1.J13, U1.K4, U1.N8, U1.N9, U1.N10, U2.9, U3.4, U3.20, U5.1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
VCC_TIER1_12V0: C37.1, C57.1, R50.2, U6.30, U15.7

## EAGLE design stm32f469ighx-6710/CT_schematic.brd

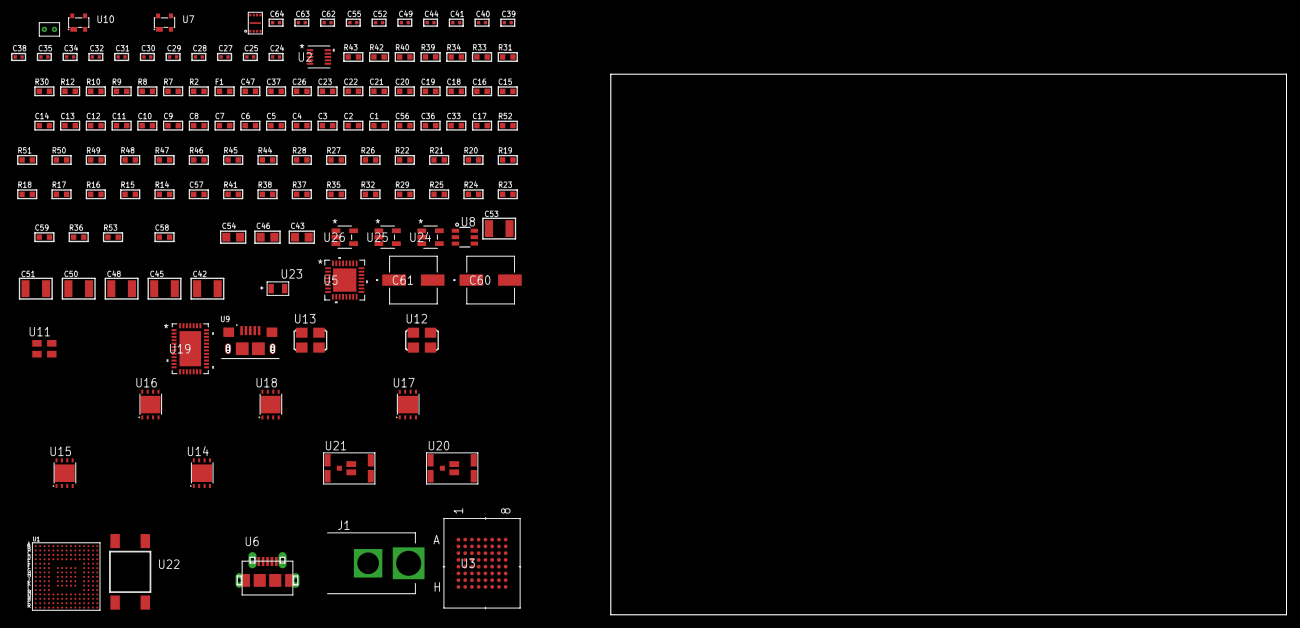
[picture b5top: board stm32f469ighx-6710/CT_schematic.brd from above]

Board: 2 copper layers, 139 parts (0 on the bottom side), 133 nets, no tracks yet.

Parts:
C1, C19, C23, C26, C37: 1e-06; C0603
C2, C3, C4, C5, C6, C7, C8, C9, C10, C11, C12, C13, C14, C15, C16, C20, C21, C22: 1e-07; C0603
C17: 4.7e-06; C0603
C18: 1e-08; C0603
C24, C25, C27, C28, C31, C32, C34, C35, C55: 1e-07; C0402
C29, C30, C38, C39, C40, C41, C44, C49, C52, C62, C63, C64: 1e-08; C0402
C33, C36, C56: 2.2e-06; C0603
C42, C45, C48, C50, C51, C53: 1e-05; C1210
C43, C46, C54: 1e-05; C0805
C47: 8e-07; R0603
C57: 2.45e-08; R0603
C58: 2.8258362168397e-09; R0603
C59: 7.105e-09; R0603
C60, C61: 0.0001; EXV-9H
F1: 240.0; L0603
J1: PJ-037B; PJ-037B_PACKAGE
R2, R31, R34, R40, R43: 1000.0; R0603
R7, R8, R9: 4700.0; R0603
R10, R12: 2200.0; R0603
R14, R15, R16, R17, R18, R19, R20, R21, R22, R27, R28, R44, R46, R47, R50, R51, R52: 10000.0; R0603
R23, R24, R25, R29, R32, R35, R37, R38, R41: 100000.0; R0603
R26: 47000.0; R0603
R30, R42: 200.0; R0603
R33: 806.0; R0603
R36: 153694.38; R0603
R39: 3900.0; R0603
R45: 75000.0; R0603
R48, R49: 95300.0; R0603
R53: 103345.45454545; R0603
U1: STM32F469IGH6; UFBGA176
U2: MAG3110FCR1; DFN-10
U3: mt28ew256aba1HPC-0SIT; LBGA-64
U4: SST26WF080BT-104I/NP; USON-8
U5: TUSB1210BRHBR; RHB32_3P45X3P45
U6: 47590-0001; MICRO_USB_AB
U7, U10: prtr5v0u2ax; SOT143B
U8: MAX4995AAUT+T; SOT-23-6
U9: 10118193-0001LF; FCI_10118193-0001LF
U11: ASEK-32.768KHz-ECST; ASEK
U12: ASFL1-19.2MHZ-NCS; ASFL1
U13: ASFL1-25MHZ-NCS; ASFL1
U14, U15, U17, U18: LP3878SDX-ADJ/NOPB; WSON-8
U16: LP2951ACSDX/NOPB; WSON-8
U19: LTC2928CUHF#PBF; QFN-38_UHF
U20, U21: IRF8306MTRPbF; IRF8306MTRPBF
U22: 4-1437565-2; SW_4-1437565-2
U23: Q65110A2395; LGM67K-G1J2-24-Z
U24, U25, U26: nc7sz125m5x; NC7SZ125M5X
U27: Dummy; DUMMY_PACKAGE_324

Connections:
CLK_U1_E1: U1.E1, U11.3
CLK_U1_G1: U1.G1, U13.3
CLK_U5_1: U5.1, U12.3
GND: C1.2, C2.2, C3.2, C4.2, C5.2, C6.2, C7.2, C8.2, C9.2, C10.2, C11.2, C12.2, C13.2, C14.2, C15.2, C16.2, C17.2, C18.2, C19.2, C20.2, C21.2, C22.2, C23.2, C24.2, C25.2, C26.2, C27.2, C28.2, C29.2, C30.2, C31.2, C32.2, C33.2, C34.2, C35.2, C36.2, C37.2, C38.2, C39.2, C40.2, C41.2, C42.2, C43.2, C44.2, C45.2, C46.2, C47.2, C48.2, C49.2, C50.2, C51.2, C52.2, C53.2, C54.2, C55.2, C56.2, C57.2, C58.2, C59.2, C60.2, C61.2, C62.2, C63.2, C64.2, J1.2, R2.2, R16.2, R26.2, R28.2, R31.2, R34.2, R37.2, R40.2, R43.2, R45.2, R48.2, R49.2, R50.2, R51.2, R52.2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
NET_U1_A5: R10.1, U1.A5, U2.7
NET_U1_B4: R12.1, U1.B4, U2.6
NET_U1_C6: R14.1, U1.C6
NET_U1_D6: R15.1, U1.D6
NET_U1_F13: C22.1, U1.F13
NET_U1_J1: R8.1, U1.J1, U25.4
NET_U1_L4: R17.1, U1.L4
NET_U1_M6: R16.1, U1.M6
NET_U1_R1: C18.1, C19.1, F1.1, U1.P1, U1.R1
NET_U1_R15: U22.3, U22.4
NET_U2_1: C24.1, U2.1
NET_U2_4: C27.1, U2.4
NET_U3_B4: R21.1, U3.B4
NET_U3_B5: R7.1, U3.B5, U24.4
NET_U5_11: R27.1, U5.11
NET_U5_12: C36.1, U5.12
NET_U5_14: R28.1, U5.14
NET_U5_20: C33.1, U5.20
NET_U5_27: R9.1, U5.27, U26.4
NET_U6_1: C37.1, U5.22, U6.1, U7.4, U8.1
NET_U6_2: U5.19, U6.2, U7.3
NET_U6_3: U5.18, U6.3, U7.2
NET_U6_4: U5.23, U6.4
NET_U8_3: R26.1, U8.3
NET_U8_4: U5.17, U8.4
NET_U14_1: C41.1, U14.1
NET_U14_6: R30.2, R31.1, U14.6
NET_U14_8: R29.1, U14.8
NET_U15_1: C44.1, U15.1
NET_U15_6: R33.2, R34.1, U15.6
NET_U15_8: R32.1, U15.8
NET_U16_5: R35.1, U16.5
NET_U16_7: R36.2, R37.1, U16.7
NET_U17_1: C49.1, U17.1
NET_U17_6: R39.2, R40.1, U17.6
NET_U17_8: R38.1, U17.8
NET_U18_1: C52.1, U18.1
NET_U18_6: R42.2, R43.1, U18.6
NET_U18_8: R41.1, U18.8
NET_U19_3: R51.1, U19.3
NET_U19_6: R48.1, U19.6
NET_U19_7: R49.1, U19.7
NET_U19_16: R50.1, R53.1, U19.16
NET_U19_18: R47.1, U19.18
NET_U19_19: R46.1, U19.19, U19.20
NET_U19_21: R44.1, R45.1, U19.21, U24.2, U25.2, U26.2
NET_U19_22: C55.1, R44.2, R46.2, R47.2, U19.11, U19.22
NET_U19_26: C58.1, U19.26
NET_U19_27: C57.1, U19.27
NET_U19_28: C59.1, U19.28
NET_U19_38: R52.1, U19.38
NET_U20_3: U19.2, U20.3
NET_U21_3: U19.37, U21.3
NET_U22_1: R2.1, U22.1, U22.2
PROC_DAC_OUT1: U1.N4, U27.2
PROC_FMC_A0: U1.E2, U3.E2
PROC_FMC_A1: U1.H3, U3.D2
PROC_FMC_A2: U1.H2, U3.C2
PROC_FMC_A3: U1.J2, U3.A2
PROC_FMC_A4: U1.J3, U3.B2
PROC_FMC_A5: U1.K3, U3.D3
PROC_FMC_A6: U1.P6, U3.C3
PROC_FMC_A7: U1.N6, U3.A3
PROC_FMC_A8: U1.R7, U3.B6
PROC_FMC_A9: U1.P7, U3.A6
PROC_FMC_A10: U1.N7, U3.C6
PROC_FMC_A11: U1.M7, U3.D6
PROC_FMC_A12: U1.L15, U3.B7
PROC_FMC_A13: U1.K15, U3.A7
PROC_FMC_A14: U1.K14, U3.C7
PROC_FMC_A15: U1.K13, U3.D7
PROC_FMC_A16: U1.N14, U3.E7
PROC_FMC_A17: U1.N13, U3.B3
PROC_FMC_A18: U1.M15, U3.C4
PROC_FMC_A19: U1.A1, U3.D5
PROC_FMC_A20: U1.B1, U3.D4
PROC_FMC_A21: U1.B2, U3.C5
PROC_FMC_A22: U1.B3, U3.B8
PROC_FMC_A23: U1.A2, U3.C8
PROC_FMC_D0: U1.M14, U3.E3
PROC_FMC_D1: U1.L14, U3.H3
PROC_FMC_D2: U1.B12, U3.E4
PROC_FMC_D3: U1.C12, U3.H4
PROC_FMC_D4: U1.R8, U3.H5
PROC_FMC_D5: U1.P8, U3.E5
PROC_FMC_D6: U1.P9, U3.H6
PROC_FMC_D7: U1.R9, U3.E6
PROC_FMC_D8: U1.P10, U3.F3
PROC_FMC_D9: U1.R10, U3.G3
PROC_FMC_D10: U1.N11, U3.F4
PROC_FMC_D11: U1.P11, U3.G4
PROC_FMC_D12: U1.R11, U3.F5
PROC_FMC_D13: U1.P15, U3.G6
PROC_FMC_D14: U1.P14, U3.F6
PROC_FMC_D15: U1.N15, U3.G7
PROC_FMC_NBL0: R22.1, U1.A4, U3.F7
PROC_FMC_NE2: R18.1, U1.C10, U3.F2
PROC_FMC_NOE: R19.1, U1.D10, U3.G2
PROC_FMC_NWAIT: U1.B11, U3.A4
PROC_FMC_NWE: R20.1, U1.C11, U3.A5
PROC_QUADSPI_BK1_IO0: U1.F14, U4.5
PROC_QUADSPI_BK1_IO1: U1.B14, U4.2
PROC_QUADSPI_BK1_IO2: R24.1, U1.K1, U4.3
PROC_QUADSPI_BK1_IO3: R25.1, U1.K2, U4.7
PROC_QUADSPI_BK1_NCS: R23.1, U1.B6, U4.1
PROC_QUADSPI_CLK: U1.L1, U4.6
PROC_USB_OTG_FS_DM: U1.C15, U9.2, U10.3
PROC_USB_OTG_FS_DP: U1.B15, U9.3, U10.2
PROC_USB_OTG_FS_VBUS: C23.1, U1.E15, U9.1, U10.4
PROC_USB_OTG_HS_ULPI_CK: U1.P4, U5.26
PROC_USB_OTG_HS_ULPI_D0: U1.R2, U5.3
PROC_USB_OTG_HS_ULPI_D1: U1.R5, U5.4
PROC_USB_OTG_HS_ULPI_D2: U1.R4, U5.5
PROC_USB_OTG_HS_ULPI_D3: U1.R12, U5.6
PROC_USB_OTG_HS_ULPI_D4: U1.R13, U5.7
PROC_USB_OTG_HS_ULPI_D5: U1.P12, U5.9
PROC_USB_OTG_HS_ULPI_D6: U1.P13, U5.10
PROC_USB_OTG_HS_ULPI_D7: U1.A6, U5.13
PROC_USB_OTG_HS_ULPI_DIR: U1.E4, U5.31
PROC_USB_OTG_HS_ULPI_NXT: U1.H4, U5.2
PROC_USB_OTG_HS_ULPI_STP: U1.M2, U5.29
VCC_12V7: C56.1, C60.1, C61.1, J1.1, R53.2, U19.23, U20.1, U20.2, U20.6, U20.7, U21.1, U21.2, U21.6, U21.7
VCC_S1_12V7: C42.1, C45.1, C47.1, C50.1, R29.2, R32.2, R38.2, U14.4, U15.4, U16.8, U17.4, U20.4, U20.5
VCC_S2_12V7: C53.1, R41.2, U18.4, U21.4, U21.5
VCC_TIER1_1V2: C21.1, C43.1, R30.1, U1.M10, U14.5
VCC_TIER1_1V8: C1.1, C2.1, C3.1, C4.1, C5.1, C6.1, C7.1, C8.1, C9.1, C10.1, C11.1, C12.1, C13.1, C14.1, C15.1, C16.1, C17.1, C20.1, C28.1, C29.1, C31.1, C34.1, C35.1, C46.1, C62.1, C63.1, C64.1, F1.2, R7.2, R8.2, R9.2, R10.2, R12.2, R14.2, R15.2, R17.2, R18.2, R19.2, R20.2, R21.2, R22.2, R23.2, R24.2, R25.2, R27.2, R33.1, U1.C1, U1.C5, U1.C7, U1.C8, U1.C9, U1.F3, U1.G3, U1.G13, U1.H13, U1.J12, U1.J13, U1.K4, U1.N8, U1.N9, U1.N10, U2.8, U3.D8, U3.F1, U4.8, U5.28, U5.30, U5.32, U15.5, U24.5, U25.5, U26.5
VCC_TIER1_3V3: C25.1, C26.1, C30.1, C32.1, C38.1, C39.1, C40.1, C48.1, R35.2, R36.1, U2.2, U3.G5, U5.21, U11.4, U12.4, U13.4, U16.1
VCC_TIER1_5V0: C51.1, R39.1, U8.5, U17.5
VCC_TIER2_1V2: C54.1, R42.1, U18.5
